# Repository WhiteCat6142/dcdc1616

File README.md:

# DCDC conveter with  NJW1616

This project aims for testing from scrach.

This is based on KiCAD 7.

### Reference
[Hardware design with RP2350](https://datasheets.raspberrypi.com/rp2350/hardware-design-with-rp2350.pdf)

[降圧スイッチング・レギュレーター NJW1616F1-AT](https://akizukidenshi.com/catalog/g/g115765/)

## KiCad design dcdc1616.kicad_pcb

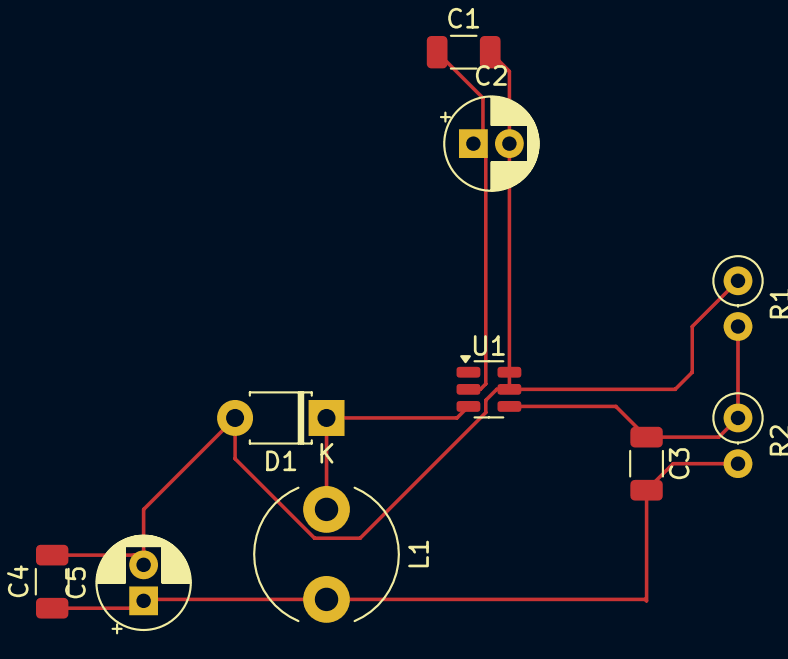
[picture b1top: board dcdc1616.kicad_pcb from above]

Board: 2 copper layers, 10 parts (0 on the bottom side), 5 nets.

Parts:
C1, C4: 10u; C_1206_3216Metric
C2, C5: 100u; CP_Radial_D5.0mm_P2.00mm
C3: 1u; C_1206_3216Metric
D1: 1S4; D_T-1_P5.08mm_Horizontal
L1: 47u; L_Radial_D7.8mm_P5.00mm_Fastron_07HCP
R1: 4.7k; R_Axial_DIN0207_L6.3mm_D2.5mm_P2.54mm_Vertical
R2: 8.2k; R_Axial_DIN0207_L6.3mm_D2.5mm_P2.54mm_Vertical
U1: NJW1616; TSOT-23-6

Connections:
0: C1.2, C2.2, C4.2, C5.2, D1.2 (A), R1.1, U1.5 (GND), U1.6 (GND)
unnamed: C3.2, C4.1, C5.1, L1.2, R2.2
unnamed: D1.1 (K), L1.1, U1.3 (SW)
unnamed: C3.1, R1.2, R2.1, U1.4 (FB)
unnamed: C1.1, C2.1, U1.2 (VIN)

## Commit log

2024-09-18 feat: add files
2024-09-18 fix: README
